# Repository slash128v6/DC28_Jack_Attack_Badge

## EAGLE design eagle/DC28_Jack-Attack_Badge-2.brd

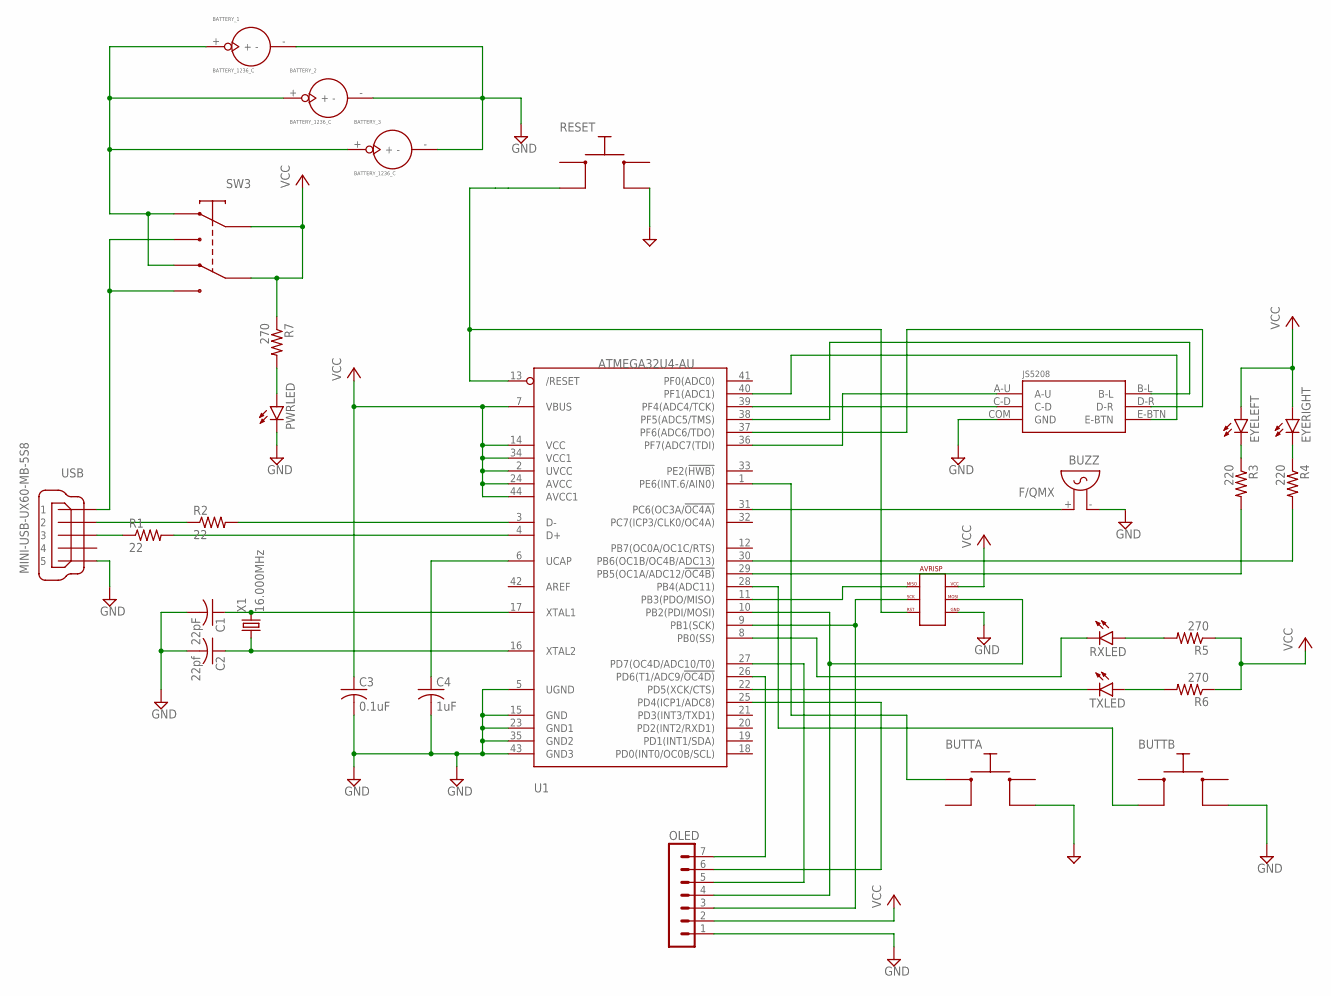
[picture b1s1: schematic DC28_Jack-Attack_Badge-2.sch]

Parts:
BATTERY_1, BATTERY_2, BATTERY_3: BATTERY_1236_C
BUTTA: PTS645; PTS645_SMD
BUTTB: PTS645; PTS645_SMD
BUZZ: F/QMX
C1: 22pF; C0805
C2: 22pf; C0805
C3: 0.1uF; C0805
C4: 1uF; C0805
EYELEFT: LED5MM
EYERIGHT: LED5MM
OLED: MA07-1
PWRLED: LEDCHIP-LED0805; CHIP-LED0805
R1, R2: 22; R0805
R3, R4: 220; R0805
R5, R6, R7: 270; R0805
RESET: PTS645; PTS645_SMD
RXLED: LEDCHIP-LED0805; CHIP-LED0805
SW3: JS202011AQN
TXLED: LEDCHIP-LED0805; CHIP-LED0805
U1: ATMEGA32U4-AU; TQFP44
U$1: AVRISP_POGO
U$2: JS5208; JS5208_PKG
USB: MINI-USB-UX60-MB-5S8; UX60-MB-5S8
X1: 16.000MHz; CSM-7X-DU

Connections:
BATT1: BATTERY_1.+, BATTERY_2.+, BATTERY_3.+, SW3.P$1 (1), SW3.P$4 (4)
GND: BATTERY_1.-, BATTERY_2.-, BATTERY_3.-, BUTTA.P$4 (4), BUTTB.P$4 (4), BUZZ.- (1), C1.2, C2.2, C3.2, C4.2, OLED.1, PWRLED.C, RESET.P$4 (4), U1.5 (UGND), U1.15 (GND), U1.23 (GND1), U1.35 (GND2), U1.43 (GND3), U$1.P$6, U$1.P$6B, U$2.COM (GND), USB.5
unnamed: R1.1, USB.3
unnamed: R2.2, U1.3 (D-)
unnamed: R2.1, USB.2
unnamed: R1.2, U1.4 (D+)
unnamed: C4.1, U1.6 (UCAP)
unnamed: BUTTA.P$1 (1), U1.1 (PE6(INT.6/AIN0))
unnamed: C2.1, U1.16 (XTAL2), X1.1
unnamed: C1.1, U1.17 (XTAL1), X1.2
unnamed: U1.36 (PF7(ADC7(TDI)), U$2.A-U
unnamed: U1.11 (PB3(PDO/MISO)), U$1.P$1, U$1.P$1B
unnamed: OLED.3, U1.9 (PB1(SCK)), U$1.P$3, U$1.P$3B
unnamed: OLED.4, U1.10 (PB2(PDI/MOSI)), U$1.P$4, U$1.P$4B
unnamed: U1.37 (PF6(ADC6/TDO)), U$2.D-R
unnamed: BUTTB.P$2 (2), U1.28 (PB4(ADC11))
unnamed: RESET.P$2 (2), U1.13 (/RESET), U$1.P$5, U$1.P$5B
unnamed: BUZZ.+ (2), U1.31 (PC6(OC3A/!OC4A))
unnamed: TXLED.C, U1.22 (PD5(XCK/CTS))
unnamed: U1.38 (PF5(ADC5/TMS)), U$2.B-L
unnamed: U1.39 (PF4(ADC4/TCK)), U$2.C-D
unnamed: R6.2, TXLED.A
unnamed: RXLED.C, U1.8 (PB0(SS))
unnamed: R5.2, RXLED.A
unnamed: U1.40 (PF1(ADC1)), U$2.E-BTN
unnamed: PWRLED.A, R7.2
unnamed: OLED.5, U1.27 (PD7(OC4D/ADC10/T0))
unnamed: OLED.6, U1.25 (PD4(ICP1/ADC8))
unnamed: OLED.7, U1.26 (PD6(T1/ADC9/!OC4D))
unnamed: R4.2, U1.30 (PB6(OC1B/OC4B/ADC13))
unnamed: R3.2, U1.29 (PB5(OC1A/ADC12/!OC4B))
unnamed: EYERIGHT.K (C), R4.1
unnamed: EYELEFT.K (C), R3.1
USB+5V: SW3.P$3 (3), SW3.P$6 (6), USB.1
VCC: C3.1, EYELEFT.A, EYERIGHT.A, OLED.2, R5.1, R6.1, R7.1, SW3.P$2 (2), SW3.P$5 (5), U1.2 (UVCC), U1.7 (VBUS), U1.14 (VCC), U1.24 (AVCC), U1.34 (VCC1), U1.44 (AVCC1), U$1.P$2, U$1.P$2B

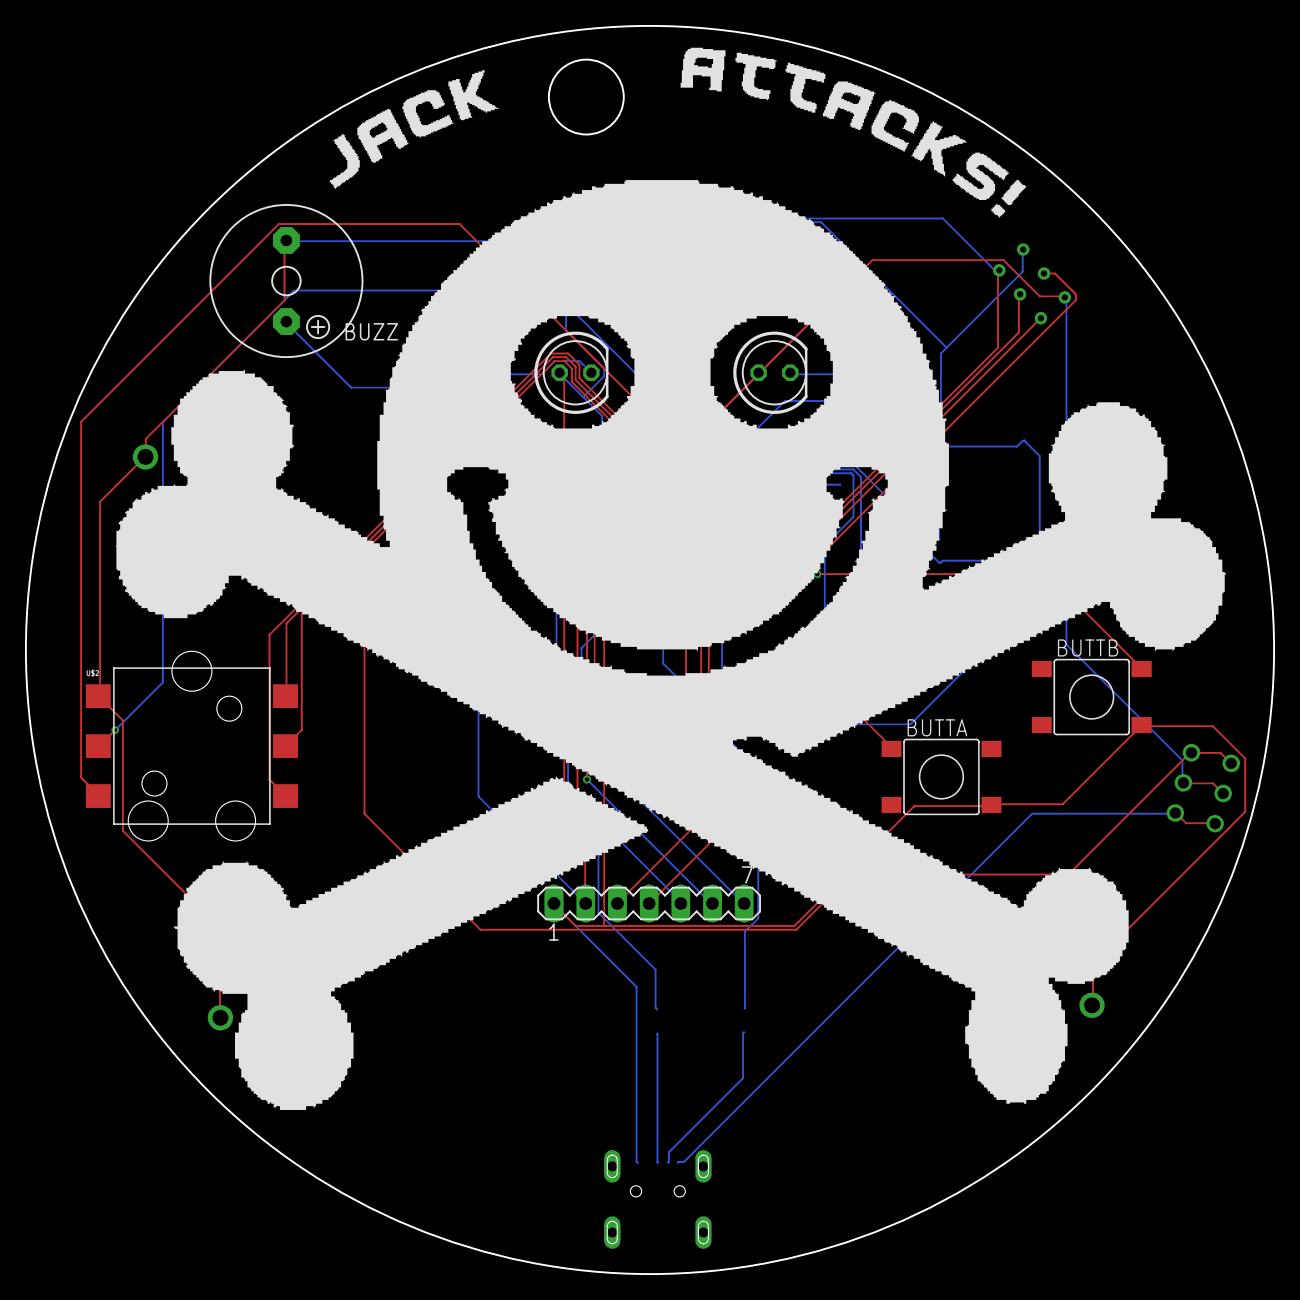
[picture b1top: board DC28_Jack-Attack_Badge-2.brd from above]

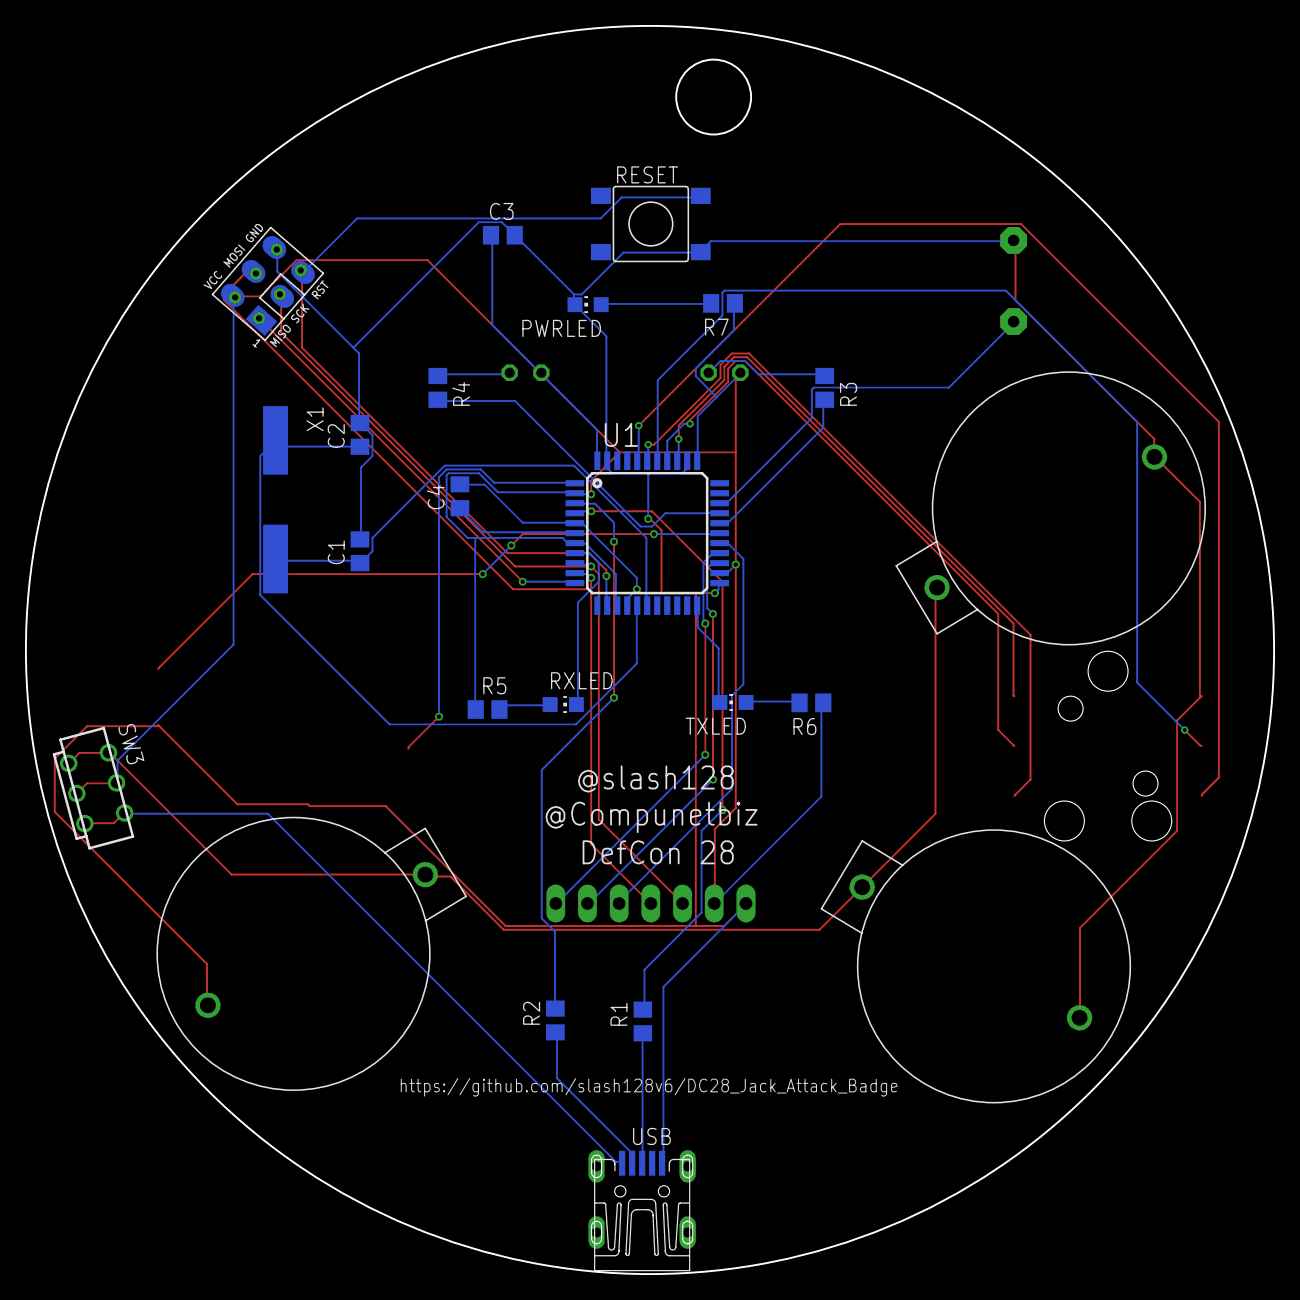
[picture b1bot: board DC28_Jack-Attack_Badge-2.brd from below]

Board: 2 copper layers, 100.0 x 100.0 mm, 30 parts (23 on the bottom side), 35 nets.

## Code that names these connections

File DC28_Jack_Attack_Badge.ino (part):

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boolean bonusLifeEligible = false;
boolean levelUpEligible = false;

#define UP A0 //PF7
#define RIGHT A1 //PF6
#define LEFT A2 //PF5
#define DOWN A3 //PF4
#define JOYBUTT A4 //PF1
#define BUTTA 7
#define BUTTB 8
#define BLUE 9 //PB5
#define RED 10 //PB6
#define GREEN 11 //PB7
#define BUZZER 5

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
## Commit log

2019-09-07 Basic game play functional
2019-09-08 Adding basic game over
2019-09-08 Arduboy pinout
2019-09-15 Arduboy Compatible
2019-11-18 Incremental commit
2019-11-27 Updated with RGB LEDs
2020-01-17 Added levelUp
2020-01-17 Refined levelUp
2020-01-18 Sound improvements
2020-01-19 Changed to C99 data types
2020-01-25 Added high score reset, cleaned up code
2020-01-25 Reduced wave level increment to 100
2020-01-26 Added Wave 10 Easter Egg
2020-01-26 Changed easter egg to wave 9
2020-02-04 Create temp
2020-02-04 Added eagle files
2021-06-16 Add files via upload
    Added SAO config
